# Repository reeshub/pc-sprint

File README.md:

# PC-SPRINT

## Navigating This Document

This README has become somewhat unwieldy, so here's an index.

- [Introduction to PC-SPRINT](#introduction-to-pc-sprint) - A quick introduction to the device and how it works.
  - [YouTube Video](#youtube-video) - A YouTube video for those who aren't keen on reading
- [Original File Listing](#original-file-listing) - The original design and accompanying files as released by Doug Severson in 1985.
- [Retro Canada KiCAD Files](#retro-canada-kicad-files) - KiCAD and gerber files drawn up by [VCFed Forum](http://www.vcfed.org/forum/forum.php) user "Retro Canada" for PCB fabrication.
- [My Own "Retro Canada" Board](#my-own-retro-canada-board) - I had a PCB fabricated and assembled it using the above files.
  - [My Testing](#my-testing) - Notes from my own tests with this board.
  - [My Benchmarks](#my-benchmarks) - Benchmarking results.
    - [Landmark](#landmark) - Results from the Landmark benchmarking tool. 
	- [TOPBENCH](#topbench) - Results from the TOPBENCH benchmarking tool.
	- [CheckIt](#checkit) - Results from the CheckIt diagnostic / benchmarking tool.
	- [MIPS](#mips) - You guessed it. Results from the MIPS benchmarking tool.
	- [Benchmarking Conclusions](#benchmarking-conclusions) - Conclusions on benchmark results.
- [Everything Else](#everything-else) - Other interesting documentation and bits and bobs.
- [License](#license) - Licensing information for this project and documentation.

## Introduction to PC-SPRINT

The PC-SPRINT is a DIY PC accelerator board design released by Doug Severson in 1985 and given away for free in computer magazines and on BBSes of the time. It is designed to allow overclocking of an [Intel 8088](Datasheets/Intel%208088%20Datasheet.pdf)-based computer such as the IBM 5150 / 5155 / 5160 PCs, PCjr, Tandy 1000, Compaq Portable<sup>*</sup>, and I'm sure a whole lot more.

It is highly recommended that the CPU be upgraded to an [NEC V20](https://en.wikipedia.org/wiki/NEC_V20) or equivalent, as the standard 8088 shipped with these early machines will probably not run at clock speeds over the original 4.77MHz. Also the 8087 co-processor, if fitted, will need to be a higher clocked version.

<sup>*</sup> The PC-SPRINT has now been tested with a Compaq Portable 1 and works great! There are a few things to bear in mind which are referenced in [issue #1](/../../issues/1). Many thanks to @cognitivegears for the excellent feedback.

In these machines and other contemporary "PC Compatibles" the system clock is usually generated by a 14.318MHz crystal connected to an [Intel 8284A](Datasheets/Intel%208284A-1%20Datasheet.pdf) Clock Generator Driver. The 8284A divides the crystal's signal by 3 giving us our 4.77MHz clock. Unfortunately we can't just replace the crystal on the motherboard as this would play havoc with all sorts of things. The basis of this accelerator is to provide an additional, faster crystal coupled with an additional 8284A to generate a faster clock signal that will be used exclusively by the CPU.

The PC-SPRINT also adds a "Turbo" switch as found on later PCs to enable / disable the higher clock rate and a hardware reset button, which is lacking on the IBM 5150. The included [WARMBOOT.COM](WARMBOOT.COM) utility sets a BIOS flag which skips the RAM test on a warm boot, making the reset very fast even at stock speed.

When the PC-SPRINT is built with the designer's recommended 22.11MHz crystal the CPU will run at a clock speed of 7.37MHz giving an impressive 64% processing speed increase (on paper). Faster speeds may be possible with faster crystals but were not recommended for stability reasons. Note that in order to utilise this accelerator the original 4.77MHz 8088 CPU must be replaced with either a faster version of the same CPU (e.g. 8088-2) or equivalent clone (e.g. [NEC V20](https://en.wikipedia.org/wiki/NEC_V20), which is highly recommended as it brings other benefits).

Much more information is available in the [original documentation](PCSPRINT.DOC) ([PDF](PCSPRINT.DOC.PDF)).

### YouTube Video

I have now also put together a short introductory video. Unfortunately it can't be embedded here, so please click the image below to be taken to YouTube:

## Original File Listing

Here is a rough index of the files included with the package as originally distributed:

- [1STREAD.ME](1STREAD.ME) - Listing of project files (you're reading a modern adaptation of this)
- [ARTWRK1X.BOT](ARTWRK1X.BOT) - Bottom layer printed circuit artwork 1x size (obsolete printer format) ([PDF](ARTWRK1X.BOT.PDF))
- [ARTWRK1X.TOP](ARTWRK1X.TOP) - Top layer printed circuit artwork 1x size (obsolete printer format) ([PDF](ARTWRK1X.TOP.PDF))
- [ARTWRK2X.BOT](ARTWRK2X.BOT) - Bottom layer printed circuit artwork 2x size (obsolete printer format) ([PDF](ARTWRK2X.BOT.PDF))
- [ARTWRK2X.TOP](ARTWRK2X.TOP) - Top layer printed circuit artwork 2x size (obsolete printer format) ([PDF](ARTWRK2X.TOP.PDF))
- [FEEDTHRU](FEEDTHRU) - Top - bottom "feed through" connection diagram ([PDF](FEEDTHRU.PDF))
- [NOPRTYCK.COM](NOPRTYCHK.COM) - Program to disable parity checks
- [PARTLIST](PARTLIST) - Parts list & placement drawing ([PDF](PARTLIST.PDF))
- [PCSPRINT.BAT](PCSPRINT.BAT) - Batch file to print PC-SPRINT info & drawings 
- **[PCSPRINT.DOC](PCSPRINT.DOC) - Description & construction info ([PDF](PCSPRINT.DOC.PDF))**
- [SCHEMATC](SCHEMATC) - Electronic circuit diagram ([PDF](SCHEMATC.PDF))
- [WARMBOOT.COM](WARMBOOT.COM) - Program to set "warm boot" flag

Note that some files have PDF conversions which were included with the version of the package as received by myself, so I have also linked those above.

The author was keen to include the original unmodified package of files with future revisions, so it is available in [pcsprint_1985.zip](References/pcsprint_1985.zip).

## Retro Canada KiCAD Files

A Vintage Computer Federation forum user by the name of Retro Canada [redrew the original PCB design in KiCAD](http://www.vcfed.org/forum/showthread.php?60803-I-overclocked-my-IBM-5150) and [released the files freely](https://sites.google.com/site/tandycocoloco/dropbox/PC-SPRINT.zip) on November 26th 2017.

I have added a mirror of this KiCAD project [here](Retro%20Canada/PC-SPRINT.zip). The package includes gerber files so KiCAD is not required if you are planning on sending the files directly to a PCB fabricator.

The user built their own based on these files (pictured above - [more of their pictures here](Retro%20Canada/Images)) but could only get it to run reliably up to a 17.43MHz crystal (CPU clock speed 5.81MHz). It is believed that this is related to DMA activity and/or RAM speed, however without the rest of their system specs it's hard to be sure.

### My Own "Retro Canada" Board

I also successfully built and tested a PC-SPRINT using Retro Canada's files. I used [PCBWay](https://www.pcbway.com/) for my PCB fabrication. Mine has a 21.47727MHz HC-49S crystal giving a CPU clock speed of 7.16MHz - the same as the popular [Tandy 1000 EX and HX](https://en.wikipedia.org/wiki/Tandy_1000#Tandy_1000_EX_and_HX) machines. Thankfully after extensive testing I haven't run into any of the issues experienced by Retro Canada, even at this higher speed.

I have experimented with 22.11MHz and even 24MHz crystals and encountered stability issues at these speeds, so I recommend starting at 21.47MHz.

#### My Testing

Here are the specs of my IBM 5150 as tested:

|Part|Model|Notes|
|---|---|---|
|CPU|[NEC V20](https://en.wikipedia.org/wiki/NEC_V20)|4.77MHz stock / 7.16MHz "turbo" with PC-SPRINT|
|FPU|[Intel 8087-2](https://en.wikipedia.org/wiki/Intel_8087)|8087 co-processor rated up to 8MHz|
|RAM|640KB|(256KB onboard, 384KB on SixPakPlus card)<sup>*</sup>|
|Motherboard|64-256KB [Later Revision](http://www.minuszerodegrees.net/5150/motherboard/5150_motherboard_revisions.htm)|[10/27/82 BIOS](http://minuszerodegrees.net/5150/bios/5150_bios_revisions.htm)|
|HDD|XT-IDE with 512MB CompactFlash card|Running [IDE_XTP.BIN BIOS](https://www.lo-tech.co.uk/wiki/XTIDE_Universal_BIOS)|
|Graphics|IBM CGA<sup>**</sup>||
|Network|3com EtherLink II||
|Floppy|2x Tandon 360KB 5.25"|Stock IBM Floppy ISA interface|
|PSU|Standard 110VAC / 63.5W|
|Operating System|[IBM PC DOS 2000](https://winworldpc.com/product/pc-dos/2000)||

<sup>\* All RAM chips were recently replaced with "New Old Stock" [Samsung KM4164B-15](http://www.minuszerodegrees.net/memory/4164.htm) parts, which have a 150ns access time.</sup>
<sup>\** I have since upgraded to an IBM EGA card (with RAM expansion) and can confirm that the PC-SPRINT works great with this setup. Benchmarks below use the CGA card.</sup>

I have done extensive testing with the above system and had no problems whatsoever. I was expecting issues with DMA activity as others have reported, however have seen none at all. Perhaps this is due to the XT-IDE and its [unusual handling of DMA](https://www.lo-tech.co.uk/xt-cfv3-dma-transfer-mode/). The PC even boots up fine with the turbo mode engaged. Incidentally, cold boot time is 1:02 stock vs. 43 seconds in turbo mode.

The included NOPRTYCHK and WARMBOOT utilities work exactly as advertised with no issues as does the new reset button.

The picture below shows how I installed the turbo and reset buttons in the case. Both are 12mm panel mount push buttons - the turbo button is a latching version:

### My Benchmarks

I ran through a series of benchmarking applications in both turbo and non-turbo mode.

These screenshots (and the videos on [my YouTube channel](https://www.youtube.com/ctrlaltrees)) were captured with a rather elaborate capture setup involving a [CGA2RGB](https://gglabs.us/node/2063), [OSSC](https://videogameperfection.com/products/open-source-scan-converter/) and a [StarTech USB3HDCAP](https://www.startech.com/uk/AV/Converters/Video/usb-3-0-video-capture-device-hdmi-dvi-vga~USB3HDCAP), but that's a tale for another time.

These benchmarks compare the performance of the NEC V20 CPU in stock 4.77MHz and turbo 7.16MHz modes using the PC-SPRINT. Unfortunately I don't have the original Intel 8088 CPU anymore to be able to test, however for some indication of how this system performs compared to a stock 5150 take a look at the [MIPS](#mips) benchmark below.

With the exception of CheckIt, all of these benchmarking tools were downloaded from the [TOPBENCH Other Benchmarks](https://dosbenchmark.wordpress.com/otherbenchmarks/) page.

#### Landmark

Landmark System Speed Test was released in 1984 by Landmark Research Internation Corporation and was one of the first DOS benchmarking tools. Here I'm using version 6.00, the final release from 1993.

|Benchmark|V20 Stock|V20 Turbo|Improvement|
|---|---|---|---|
|CPU<sup>*</sup>|3.02MHz|4.60MHz|52.32%|
|FPU|4.56MHz|6.92MHZ|51.75%|
|Video|412.35 chr/ms|446.03 chr/ms|8.17%|

<sup>\* The way this figure is calculated is interesting (and generally considered wrong) but the percentage increase is all that matters to us. There is more information on the way Landmark arrives at their CPU figure [here](https://dosbenchmark.wordpress.com/research/landmark/).

#### TOPBENCH

[TOPBENCH](https://dosbenchmark.wordpress.com/) is a modern realtime DOS benchmarking tool. An interesting feature is its "database", which allows you to compare your system's performance to that submitted by other users. I'm using version 0.38 with the full database.

Note that TOPBENCH reports the run times of its tests in microseconds, so a lower score is better (faster).

|Benchmark|V20 Stock|V20 Turbo|Improvement|
|---|---|---|---|
|TOPBENCH Score|5|7|2|
|MemTest|2488μ|1640μ|51.71%|
|MemEA|1863μ|1211μ|53.84%|
|Opcodes|1519μ|991μ|53.28%|
|VidMem|2009μ|1840μ|9.18%|
|3DGames|1408μ|919μ|53.21%|
|Total|9287μ|6601μ|40.69%|

According to the database we've gone from an NCR PC4 to an Olivetti PC-1. As I'm not familiar with either of these machines I guess I'll just have to take their word for it. ;)

#### CheckIt

From [WinWorldPC](https://winworldpc.com/product/checkit/30), who said it better than I ever could:

CheckIt, from TouchStone Software Corporation, is a diagnostic tool for generic PC/XT/AT compatible computers. It can perform tests on RAM, hard disks, video cards, floppy disks, motherboard resources, and I/O devices. It has an easy to use menu interface but can also run tests non-interactively.

I'm running version 3, the last release from 1990. In each of these screenshots the "Stock" value (top grey line) is the NEC V20 with turbo mode off.

|Benchmark|V20 Stock|V20 Turbo|Improvement|
|---|---|---|---|
|CPU [Dhrystones](https://en.wikipedia.org/wiki/Dhrystone)|387|597|54.26%|
|FPU [Whetstones](https://en.wikipedia.org/wiki/Whetstone_(benchmark))|123.1K|186K|51.1%|

|Benchmark|V20 Stock|V20 Turbo|Improvement|
|---|---|---|---|
|Transfer Speed|198.9K/sec|303.2K/sec|52.44%|
|Average Seek Time<sup>*</sup>|1.7ms|1.1ms|54.55%|
|Track Seek Time<sup>*</sup>|1.7ms|1.1ms|54.55%|

<sup>\* Note that when it comes to seek times, lower numbers are better.</sup>

|Benchmark|V20 Stock|V20 Turbo|Improvement|
|---|---|---|---|
|BIOS Video Speed|637chr/sec|968chr/sec|51.96%|
|Direct Video Speed|4837chr/sec|7395chr/sec|52.88%|

I also ran various RAM tests with turbo enabled to see if it would pick up any errors, but all tests passed with no problems.

#### MIPS

Chips & Technologies MIPS was written by Jim Bracking and released in 1986. It's a very comprehensive test covering various number-crunching operations, and even shows your score compared to typical examples of machines of that era - an IBM PC, PC/AT and a Compaq 386.

|Benchmark|V20 Stock|V20 Turbo|Improvement|
|---|---|---|---|
|General Instructions|0.19|0.29|52.63%|
|Integer Instructions|0.32|0.49|53.12%|
|Memory To Memory|0.26|0.41|57.69%|
|Register To Register|0.39|0.60|53.85%|
|Register To Memory|0.33|0.51|54.55%|
|Overall Performance|0.30|0.46|53.33%|

MIPS also shows that our overclocked NEC V20 is over twice as fast as a stock IBM 5150 running an Intel 8088 CPU.

### Benchmarking Conclusions

As we can see, the speedup on all fronts is in the region of 50-55%, which is a massive improvement for around £6 worth of components. According to [MIPS](#mips), with the addition of the V20 and the overclock this machine is now twice as fast as a standard IBM PC. I haven't encountered any stability issues but my testing is ongoing and of course, if I come across them I will document them here.

Finally, of course benchmarks are entirely artificial and don't necessarily reflect real world results. In my testing I have found that, without exception, every single game on this machine (and I have a fair few) is more playable with massively reduced slowdowns and stuttering. That's a hard thing to quantify, however, so with that in mind I am working on a series of comparison videos which should hopefully be available [on my YouTube channel](https://www.youtube.com/ctrlaltrees) soon.

There is now [a general overview of my overclocked IBM 5150 on YouTube](https://youtu.be/Y7NNCWvt1nY) for anyone interested.

### Everything Else

Here I'll collect any other odd bits of info I can find on the PC-SPRINT.

[pcspnt.txt](Everything%20Else/Documents/pcspnt.txt) - PC-SPRINT 1000 by Charles Robertson (1988-08-13). Information relating to the installation of the PC-SPRINT in the Tandy 1000A. \[[source](http://www.oldskool.org/guides/tvdog/documents.html)\]

## License

The PC-SPRINT was originally released with the following licensing conditions:

> License to duplicate, distribute and use PC-SPRINT is hereby granted to individuals, for personal use, and non-profit organizations with the following conditions:
> 
> 1. All files in this package must be distributed intact and unmodified.
> 2. No fees may be charged (other than reasonable duplication costs) for this package or any printed circuit board made by its use.
> 3. All commercial rights to this package remain the property of the author.
> 4. Hobby or user oriented magazines may reprint all or portions of this package, as long as credit is given to the author.
> 5. For-profit organizations may obtain a license by contacting the author.
> 6. The author will not be held liable for any damages or injuries, direct or subsequent, that may result from its distribution, construction, installation or use.

Attempts have been made to track down the author but to no avail, so this project is shared here in good faith that the sentiments of the original designer will be honoured.

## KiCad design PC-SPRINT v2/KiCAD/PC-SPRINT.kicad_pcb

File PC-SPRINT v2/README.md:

# PC-SPRINT v2

Building on the work of Doug Severson from 1985, the PC-SPRINT v2 is an updated and improved DIY Open Hardware overclocking device for 8088-based systems. Please see the [PC-SPRINT README](/README.md) for an introduction to the original device.

With the potential for DMA-related problems I decided that it would be worth attempting to improve the design of the PC-SPRINT. Although I haven't run into these problems myself at the recommended clock speed of 7.37MHz it will be a fun project and an opportunity to teach myself some things about KiCAD, PCB fabrication and early PCs. With all that in mind, the PC-SPRINT v2 will aim to seamlessly switch back to the stock clock speed whenever there is DMA activity, hopefully eliminating the possibility of lockups.

To understand why and how, we'll start with a quick history lesson.

In 2014 fellow VCFed forum user [Sergey Kiselev](https://github.com/skiselev), author of various high profile 8088 and Z80 hardware projects, analysed the PC-SPRINT and [observed](http://www.vcfed.org/forum/showthread.php?41940-IBM-XT-cpu-upgrade&p=319044#post319044) that it didn't disable the turbo mode when the system was performing DMA activity, as per other "turbo" PC clones. [DMA or "Direct Memory Access"](https://en.wikipedia.org/wiki/Direct_memory_access) is a way for devices to read and write directly to RAM, bypassing the CPU. If the device in question isn't designed to take account of the CPU running at a different clock speed to the rest of the system this can result in potential problems. Based on this, Sergey went on to design and release his own solution, the [Turbo 8088](../References/Turbo%208088%20-%20Schematic.pdf), based on his [Xi 8088](http://www.malinov.com/Home/sergeys-projects/xi-8088) ISA processor board.

In 2019, yet another VCFed forum user, inmbolmie, [decided to build one](http://www.vcfed.org/forum/showthread.php?70923-IBM-5160-overclock-Sergey%92s-way), as well as fixing some bugs in Sergey's design. The updated version was dubbed the [Turbo8088 v2](../References/turbo8088%20v2.pdf). The board was successfully tested in a 5160 at up to 25MHz giving an impressive 8.33MHz CPU clock. Over this speed various problems were reported.

As you can see, the Turbo8088 is a large design that adds a lot of components and complexity. I don't want to tread on Sergey's toes as he's one of the best when it comes to systems architecture and electronics but I decided to see whether it would be possible to incorporate the DMA signals Sergey identified into the PC-SPRINT, making for a simple and compact hybrid solution.

I believe that I have succeeded in this, and my PC-SPRINT v2 prototypes are currently being tested.

As this started life as a freely available project it only seemed right to release the PC-SPRINT v2 under the GPL. The package includes the KiCAD and gerber files for PCB fabrication. This is an ongoing project and this repo will be regularly updated as new information comes to light from ongoing research and testing.

~~The PC-SPRINT v2 files are available [here](KiCAD).~~
I came up against some problems during some testing that will require a minor redesign. I have decided to make the v2 files unavailable until I at least have a working prototype. For now, if you want a PC-SPRINT, I highly recommend you go build [the original version](../). They're great!

## DMA Signals on the 5150 Motherboard

After confirming using the [IBM Technical Reference](../References/IBM_5150_Technical_Reference_6322507_APR84.pdf), I believe that we can pick these up from what are essentially the same locations as Sergey's design for the 5160. The Turbo8088 and indeed the PC-SPRINT v2 would then be able to incorporate the following:

- HRQDMA: From pin 10 of the Intel 8237 DMA controller IC. This pin goes HIGH on DMA activity. This part is labelled U35 on the 5150 motherboard. If an AMD part is used (as in my case) it will be have the part number Am9517A.
- HRQWAIT: From pin 7 of an 74LS175 IC. As above, this pin also goes HIGH on DMA activity. This part is labelled U98 on the 5150 motherboard - note that it is inaccessible with the motherboard in place due to the floppy drive bays.

The above picture is taken courtesy of inmbolmie's 5160 installation for the Turbo8088, however these are essentially identical for the 5150. I will update with my own picture when I get a chance to get one.

On the PC-SPRINT v2, these inputs are connected to a new NOR gate along with the turbo button.This should give us the required logic to switch to the lower clock speed if either of these inputs go HIGH. Of course this reverses the function of the turbo button, but it's no big deal (most turbo buttons "back in the day" worked this way anyway).

## Current Status

Here are the specs of my IBM 5150 as tested:

|Part|Model|Notes|
|---|---|---|
|CPU|[NEC V20 / D70108C-10](https://en.wikipedia.org/wiki/NEC_V20)|Rated up to 10MHz. 4.77MHz stock / 8MHz "turbo" with PC-SPRINT v2.|
|FPU|[Intel 8087-1](https://en.wikipedia.org/wiki/Intel_8087)|8087 co-processor rated up to 10MHz.|
|RAM|640KB (150ns)|(256KB onboard, 384KB on SixPakPlus card)<sup>*</sup>|
|Motherboard|64-256KB [Later Revision](http://www.minuszerodegrees.net/5150/motherboard/5150_motherboard_revisions.htm)|[10/27/82 BIOS](http://minuszerodegrees.net/5150/bios/5150_bios_revisions.htm)|
|HDD|XT-IDE with 512MB CompactFlash card|Running [IDE_XTP.BIN BIOS](https://www.lo-tech.co.uk/wiki/XTIDE_Universal_BIOS)|
|Graphics|IBM EGA||
|Network|3com EtherLink II||
|Floppy|2x Tandon 360KB 5.25"|Stock IBM Floppy ISA interface|
|PSU|Standard 110VAC / 63.5W|
|Operating System|[IBM PC DOS 2000](https://winworldpc.com/product/pc-dos/2000)||

<sup>\* All RAM chips were recently replaced with "New Old Stock" [Samsung KM4164B-15](http://www.minuszerodegrees.net/memory/4164.htm) parts, which have a 150ns access time.</sup>

The PCBs have arrived from [PCBWay](https://www.pcbway.com/) and the v2 is currently undergoing testing. The new design is around 20mm longer than the original, meaning that it now extends underneath the left hand floppy / hard drive (if fitted). Thankfully there is plenty of clearance, however it is recommended that the board is assembled with 90 degree pin headers on J1 and J2 (as pictured below) as there is minimal space for the cables to protrude upwards. The PCB design may be modified in future but this is not a current priority.

**The PC-SPRINT v2 is working as intended but without the J2 DMA pins connected. This means that it is permanently in turbo mode and may cause problems with DMA transfers.**

The next step will be to get these connected up and tested. For now, based on my experience, the PC-SPRINT (v1 or v2) with a 22.11MHz crystal is a perfectly safe and worthwhile upgrade - at least with my system as documented above.

## Timing Crystal Values Tested

These are the values I have tested in my system so far. Your results may differ.

|Crystal Value|CPU Clock Speed|Result|Notes|
|---|---|---|---|
|21.4772MHz|7.16MHz|Working|Same clock speed as [Tandy 1000 EX and HX](https://en.wikipedia.org/wiki/Tandy_1000#Tandy_1000_EX_and_HX).|
|22.1184MHz|7.37MHz|Working|This is the original PC-SPRINT recommended value.|
|24MHz|8MHz|System will not boot / lockups when enabled<sup>*</sup>|Same clock speed as later [IBM PC/AT](https://en.wikipedia.org/wiki/IBM_Personal_Computer/AT).|

<sup>\*</sup> I was initially testing with a D70108C-5, which is the 5MHz version of the NEC V20. When swapping to a D70108C-10, the system will at least allow me to run some benchmarks, however it is very unstable when loading applications. It even more unstable with the 8087-2 FPU installed. This is the 8MHz part, however I have a 10MHz-capable 8087-1 on its way to me for further testing. I'm hoping that [hooking up the DMA signals](#dma-ignals-on-the-5150-motherboard) will alleviate these issues.

For more information on timing please see the [original PC-SPRINT documentation](/blob/master/README.md) for now.

## Benchmarks

Here are some screenshots taken with the PC-SPRINT running at 8MHz. This is a work in progress. For much more comprehensive benchmarks at a more sensible (working) speed please see the [PC-SPRINT README](/README.md).

### MIPS

Chips & Technologies MIPS was written by Jim Bracking and released in 1986. It's a very comprehensive test covering various number-crunching operations, and even shows your score compared to typical examples of machines of that era - an IBM PC, PC/AT and a Compaq 386.

Turbo disabled on the left, enabled on the right.

|Benchmark|V20 Stock|V20 Turbo|Improvement|
|---|---|---|---|
|General Instructions|0.19|0.32|68.42%|
|Integer Instructions|0.32|0.55|71.88%|
|Memory To Memory|0.26|0.46|76.92%|
|Register To Register|0.39|0.67|71.79%|
|Register To Memory|0.33|0.58|75.76%|
|Overall Performance|0.30|0.52|73.33%|

MIPS also shows that our overclocked NEC V20 is over twice as fast as a stock IBM 5150 running an Intel 8088 CPU.

### CheckIt

From [WinWorldPC](https://winworldpc.com/product/checkit/30), who said it better than I ever could:

CheckIt, from TouchStone Software Corporation, is a diagnostic tool for generic PC/XT/AT compatible computers. It can perform tests on RAM, hard disks, video cards, floppy disks, motherboard resources, and I/O devices. It has an easy to use menu interface but can also run tests non-interactively.

I'm running version 3, the last release from 1990. In each of these screenshots the "Stock" value (top grey line) is the NEC V20 measured with turbo mode off.

|Benchmark|V20 Stock|V20 Turbo|Improvement|
|---|---|---|---|
|CPU [Dhrystones](https://en.wikipedia.org/wiki/Dhrystone)|387|664|71.58%|
|FPU [Whetstones](https://en.wikipedia.org/wiki/Whetstone_(benchmark))<sup>*</sup>|123.1K|13.1K|-89.36%|

<sup>\* Note that the 8087-2 is incredibly unstable at this clock speed so I had to remove it for this test, hence the huge decrease in performance on this test. Realistically, [not much uses the 8087](https://ctrl-alt-rees.com/2019-06-06-list-of-software-that-utilizes-intel-8087-math-coprocessor-fpu.html), but I have a faster one on order anyway.</sup>

|Benchmark|V20 Stock|V20 Turbo|Improvement|
|---|---|---|---|
|Transfer Speed|198.9K/sec|342.5K/sec|72.2%|
|Average Seek Time<sup>*</sup>|1.7ms|1ms|70%|
|Track Seek Time<sup>*</sup>|1.7ms|1ms|70%|

<sup>\* Note that when it comes to seek times, lower numbers are better.</sup>

|Benchmark|V20 Stock|V20 Turbo|Improvement|
|---|---|---|---|
|BIOS Video Speed|788chr/sec|1389chr/sec|76.27%|
|Direct Video Speed|4930chr/sec|8464chr/sec|71.68%|

I also ran various RAM tests with turbo enabled to see if it would pick up any errors, but, perhaps surprisingly, all tests actually passed with no problems.

### Benchmarking Conclusions

As it stands, without the DMA side of things hooked up, I can highly recommend *against* the 24MHz crystal. However the benchmarks are pretty tantalising and show that this is definitely worth pursuing further - a 70% increase in performance is certainly better than a 50-55% increase [as originally measured](/README.md), after all!

## License

The original  design was released under a license similar to the modern-day GPL (IANAL), so I have attached that license here. The PC-SPRINT v2 is therefore assumed to comply with the [Open Hardware Specification](https://en.wikipedia.org/wiki/Open-source_hardware).

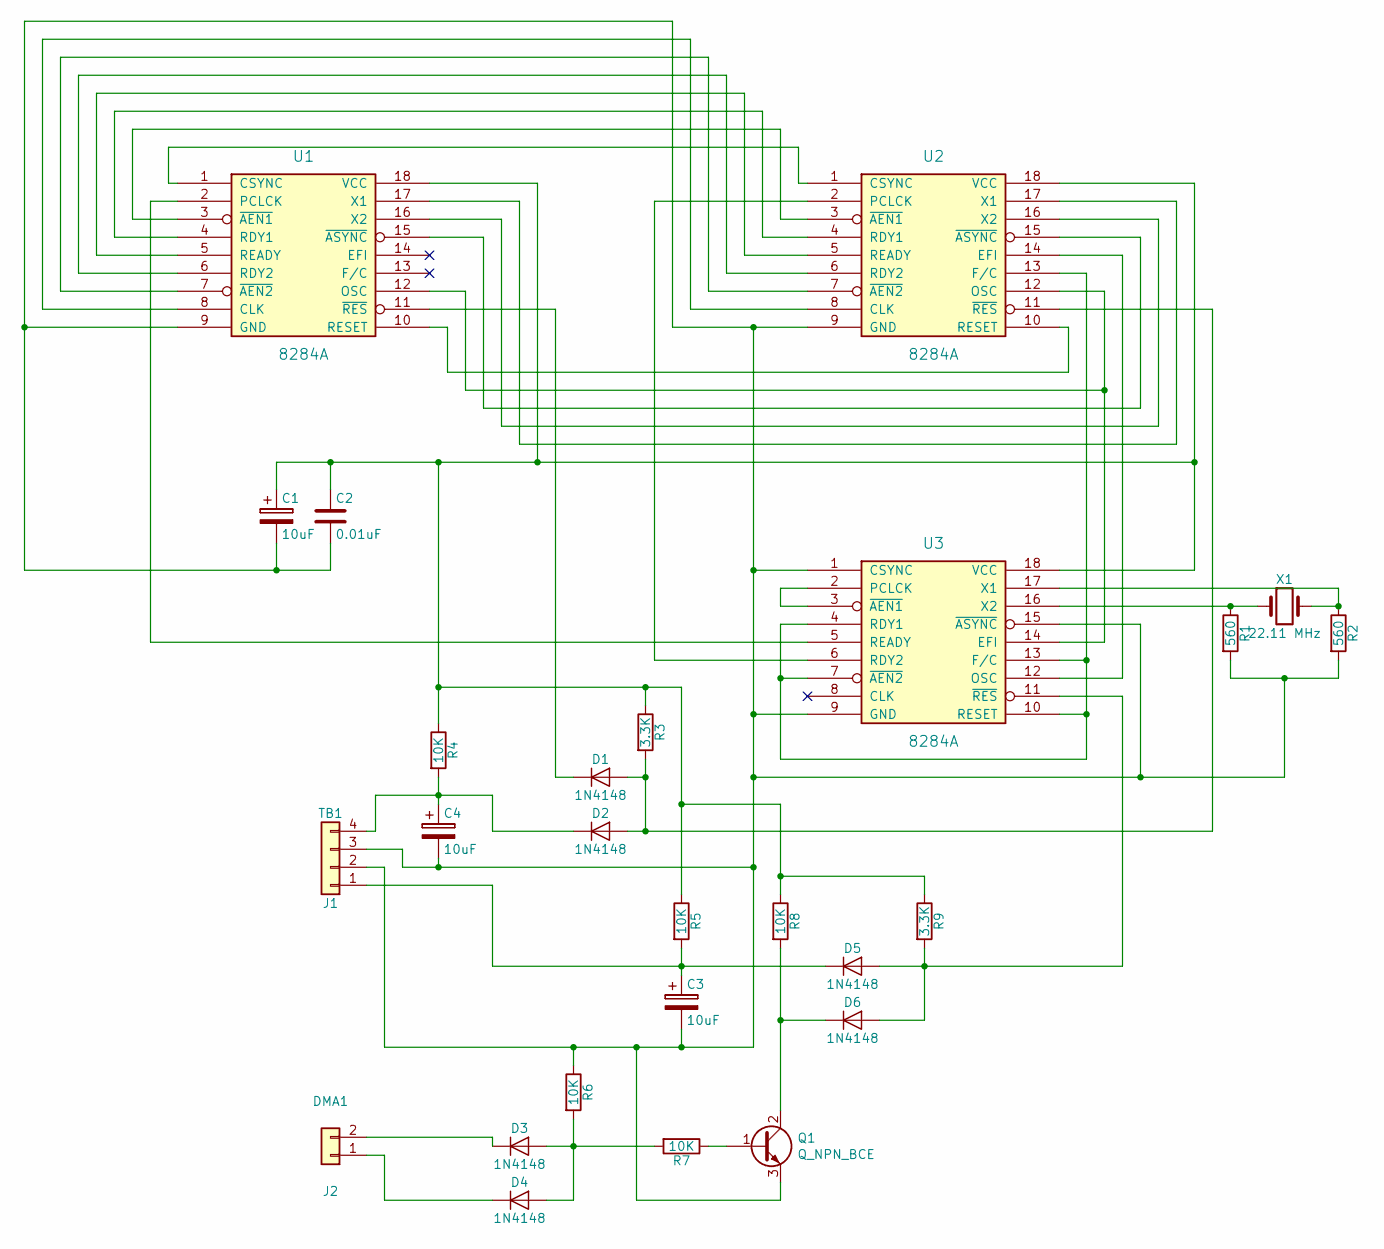
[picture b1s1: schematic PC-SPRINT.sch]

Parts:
C1, C3, C4: 10uF; CP_Radial_Tantal_D4.5mm_P2.50mm
C2: 0.01uF; C_Disc_D5.0mm_W2.5mm_P2.50mm
D1, D2, D3, D4, D5, D6: 1N4148; D_DO-35_SOD27_P7.62mm_Horizontal
J1: TB1; PinSocket_1x04_P2.54mm_Vertical
J2: DMA1; PinSocket_1x02_P2.54mm_Vertical
Q1: Q_NPN_BCE; TO-92_Molded_Wide_Oval
R1, R2: 560; R_Axial_DIN0204_L3.6mm_D1.6mm_P7.62mm_Horizontal
R3, R9: 3.3K; R_Axial_DIN0204_L3.6mm_D1.6mm_P7.62mm_Horizontal
R4, R5, R6, R7, R8: 10K; R_Axial_DIN0204_L3.6mm_D1.6mm_P7.62mm_Horizontal
U1, U2, U3: 8284A; DIP-18_W7.62mm_LongPads
X1: 22.11 MHz; Crystal_HC18-U_Vertical

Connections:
unnamed: C1.1, C2.1, R3.1, R4.1, R5.1, R8.1, R9.1, U1.18 (VCC), U2.18 (VCC), U3.18 (VCC)
unnamed: C1.2, C2.2, C3.2, C4.2, J1.2, J1.3, Q1.3 (E), R1.2, R2.2, R6.1, U1.9 (GND), U2.9 (GND), U3.1 (CSYNC), U3.9 (GND), U3.15 (~ASYNC)
unnamed: C3.1, D5.1 (K), J1.1, R5.2
unnamed: C4.1, D2.1 (K), J1.4, R4.2
unnamed: D1.1 (K), U1.11 (~RES)
unnamed: D1.2 (A), D2.2 (A), R3.2, U2.11 (~RES)
unnamed: D3.1 (K), J2.2
unnamed: D3.2 (A), D4.2 (A), R6.2, R7.2
unnamed: D4.1 (K), J2.1
unnamed: D5.2 (A), D6.2 (A), R9.2, U3.11 (~RES)
unnamed: D6.1 (K), Q1.2 (C), R8.2
unnamed: Q1.1 (B), R7.1
unnamed: R1.1, U3.16 (X2), X1.1
unnamed: R2.1, U3.17 (X1), X1.2
unnamed: U1.1 (CSYNC), U2.1 (CSYNC)
unnamed: U1.2 (PCLCK), U3.5 (READY)
unnamed: U1.3 (~AEN1), U2.3 (~AEN1)
unnamed: U1.4 (RDY1), U2.4 (RDY1)
unnamed: U1.5 (READY), U2.5 (READY)
unnamed: U1.6 (RDY2), U2.6 (RDY2)
unnamed: U1.7 (~AEN2), U2.7 (~AEN2)
unnamed: U1.8 (CLK), U2.8 (CLK)
unnamed: U1.10 (RESET), U2.10 (RESET)
unnamed: U1.12 (OSC), U2.12 (OSC), U3.14 (EFI)
unnamed: U1.15 (~ASYNC), U2.15 (~ASYNC)
unnamed: U1.16 (X2), U2.16 (X2)
unnamed: U1.17 (X1), U2.17 (X1)
unnamed: U2.2 (PCLCK), U3.6 (RDY2)
unnamed: U2.13 (F/C), U3.4 (RDY1), U3.7 (~AEN2), U3.10 (RESET), U3.13 (F/C)
unnamed: U2.14 (EFI), U3.12 (OSC)
unnamed: U3.2 (PCLCK), U3.3 (~AEN1)

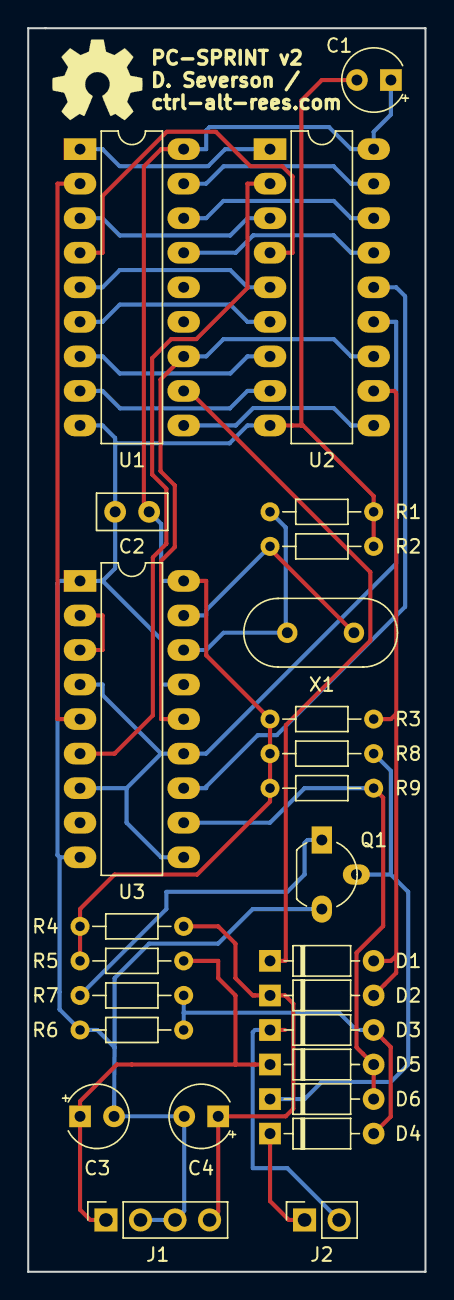
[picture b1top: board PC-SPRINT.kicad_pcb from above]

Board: 2 copper layers, 29.2 x 91.4 mm, 26 parts (0 on the bottom side), 31 nets.

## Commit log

2020-03-10 Added original 1985 files by Doug Severson
2020-03-10 Updated README and added original zip package
2020-03-10 Use bulleted list for file listing
2020-03-10 Added further description and datasheets
2020-03-10 Added note on datasheet copyright
2020-03-10 Fix datasheet links
2020-03-10 Try to fix datasheet links again (I am not good with computer)
2020-03-10 More README tweaks
2020-03-10 Yet more README tweaks
2020-03-10 Added Retro Canada release
2020-03-10 Added Retro Canada unzipped files
2020-03-10 Added PC-SPRINT v2 information and files
2020-03-10 Added Images
2020-03-10 More Images...
2020-03-10 Hopefully final updates for now
2020-03-16 Added some info based on my testing with the Retro Canada PCB, also added pics of my PCB
2020-03-16 Added Landmark Benchmark Results
2020-03-16 Tweaked Heading Sizes
2020-03-16 Added TOPBENCH Benchmark Results
2020-03-16 Added Note On How Screenshots Were Captured
2020-03-16 Added CheckIt Benchmarks
2020-03-16 Added Benchmarking Conclusions
2020-03-16 Add More Of An Intro To v2
2020-03-16 Added DMA Information For v2
2020-03-16 Add New DMA Section To Index
2020-03-16 Added Note On 7400 Logic
2020-03-18 Added MIPS Benchmark Results And A Few Other Tweaks
2020-03-18 Tweaks
2020-03-18 More Wording Tweaks
2020-03-18 Further Tweaks To Grammar & Whatnot
2020-03-18 Yet More Tweaks To Wording
2020-03-18 Update The PC-SPRINT v2 Section To Clarify Some Things
2020-03-18 More Updates To v2 Section
2020-03-18 Yet More Changes To The v2 Section
2020-03-18 Another Small Tweak To Wording
2020-03-20 Fix Typo In MIPS Results Table
2020-03-20 Separate v2 Stuff Into Its Own Area With Its Own README
2020-03-20 Move 3D Render of v2 To Correct Place
2020-03-20 Emboldening
2020-03-20 PC-SPRINT v2 Current Status Update
2020-03-20 Fix Image Link
2020-03-20 V2: Added BOM & Timing Info
2020-03-20 v2 - More Testing Info
2020-03-20 Final Tweaks For Today
2020-03-20 ...nope
2020-03-20 One More Typo
2020-03-20 Fix Some Links
2020-03-23 Added Some More Information & New Benchmarks
2020-03-23 Fix Wording
2020-03-31 Add NEC V20 Manual / Datasheet
2020-03-31 Remove PC-SPRINT v2 Info Pending Further Work
2020-06-16 Removed References To PC-SPRINT v2 As Project Is On Hold Indefinitely & Wasn't Working Anyway
2020-06-16 A Few More Tweaks To Wording
2020-06-16 Added Note on 8087
2020-06-16 Further Tweaks To Wording
2020-06-16 Added YouTube Video Link
2020-06-16 Update YouTube Image Link
2021-01-11 Added Link To 5150 Video & Random Tandy 1000A Document
2022-05-22 Added Compaq Portal 1 Feedback
2022-05-22 Compaq Portable - Fix Link To Issue
2022-05-22 Compaq Portable - Fix Bad Copy & Paste (Last Commit I promise!)

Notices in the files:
PC-SPRINT v2/README.md:
The original  design was released under a license similar to the modern-day GPL (IANAL), so I have attached that license here. The PC-SPRINT v2 is therefore assumed to comply with the [Open Hardware Specification](https://en.wikipedia.org/wiki/Open-source_hardware).
